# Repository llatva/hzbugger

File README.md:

# hzbugger

Hzbugger is an STM32F103C8T6-based Black Magic Probe compatible debugger by Lasse OH3HZB. 

Bottom side silkscreen created using AI tools (intended for *black PCB* as in pictures below). 

Basic functionality works out-of-box with BMP bluepill image. Extra LEDs and AUX header requires fw customization.
See [BlackMagic Probe adaptation guide](./blackmagic-probe-adaptation-guide.md) for firmware-porting and usage details.

## Schematic

<a href="./hzbugger-revA-schematic.pdf">hzbugger-revA-schematic.pdf</a>

## Getting started: Using Hzbugger to flash firmware

### Connect the probe

The device should enumerate as /dev/ttyACM0 and /dev/ttyACM1 (on Linux).

### Build the firmware

Build the application so that the output includes an ELF file containing debug information.
For example:

    build/my_application.elf

The ELF file is used both for programming the target and for debugging.
Start GDB from the shell:

    arm-none-eabi-gdb build/my_application.elf

### Flash the firmware

Then run the following commands inside GDB:

    target extended-remote /dev/ttyACM1
    monitor erase_mass
    load
    monitor reset

## Getting started: Using Hzbugger as debugger with Visual Studio Code (vscode)

### Required software

- Visual Studio Code
- ARM GNU Toolchain
- `arm-none-eabi-gdb`
- The Cortex-Debug VS Code extension

The firmware should be built with debug information enabled, for example:

    -g

For development builds, it is also useful to disable compiler optimization:

    -O0

This makes source-level debugging easier.

### Create the VS Code configuration

Create the following file in your project:

    .vscode/launch.json

Add debug configuration:

    {
        "version": "0.2.0",
        "configurations": [
            {
                "name": "Debug with Black Magic Probe",
                "type": "cortex-debug",
                "request": "launch",
                "servertype": "bmp",
                "executable": "${workspaceFolder}/build/my_application.elf",
                "device": "YOUR_MCU",
                "cwd": "${workspaceFolder}",
                "runToEntryPoint": "main"
            }
        ]
    }

Replace `YOUR_MCU` with the name of your target MCU.

Also update the `executable` path if your ELF file is located somewhere else.

### Start debugging

Connect Hzbugger and start the debugger in VS Code using `F5` button.
VS Code will use GDB to connect to the Hzbugger and start a debug session.
You can then use the normal VS Code debugging features:

- Set breakpoints
- Step over — `F10`
- Step into — `F11`
- Step out — `Shift+F11`
- Continue — `F5`
- Inspect variables
- Inspect the call stack
- Use the Watch window
- Inspect registers and memory

---

### Useful Commands

* Check the ARM GDB installation: `arm-none-eabi-gdb --version`
* Find the Hzbugger device: `ls /dev/ttyACM`
* Start GDB manually: `arm-none-eabi-gdb build/my_application.elf`
* Connect to the probe: `target extended-remote /dev/ttyACM1`
* Erase flash: `monitor erase_mass`
* Flash the firmware: `load`
* Reset the target: `monitor reset`

(Hzbugger acts as a GDB server itself so you do not need to start a separate (e.g. OpenOCD) GDB server)

## References

* Website of the Black Magic Probe: https://black-magic.org/
* BMP firmware repository: https://codeberg.org/blackmagic-debug/blackmagic

## LICENSE

CERN-OHL-S (strongly reciprocal), see [LICENSE.txt](./LICENSE.txt) for details.

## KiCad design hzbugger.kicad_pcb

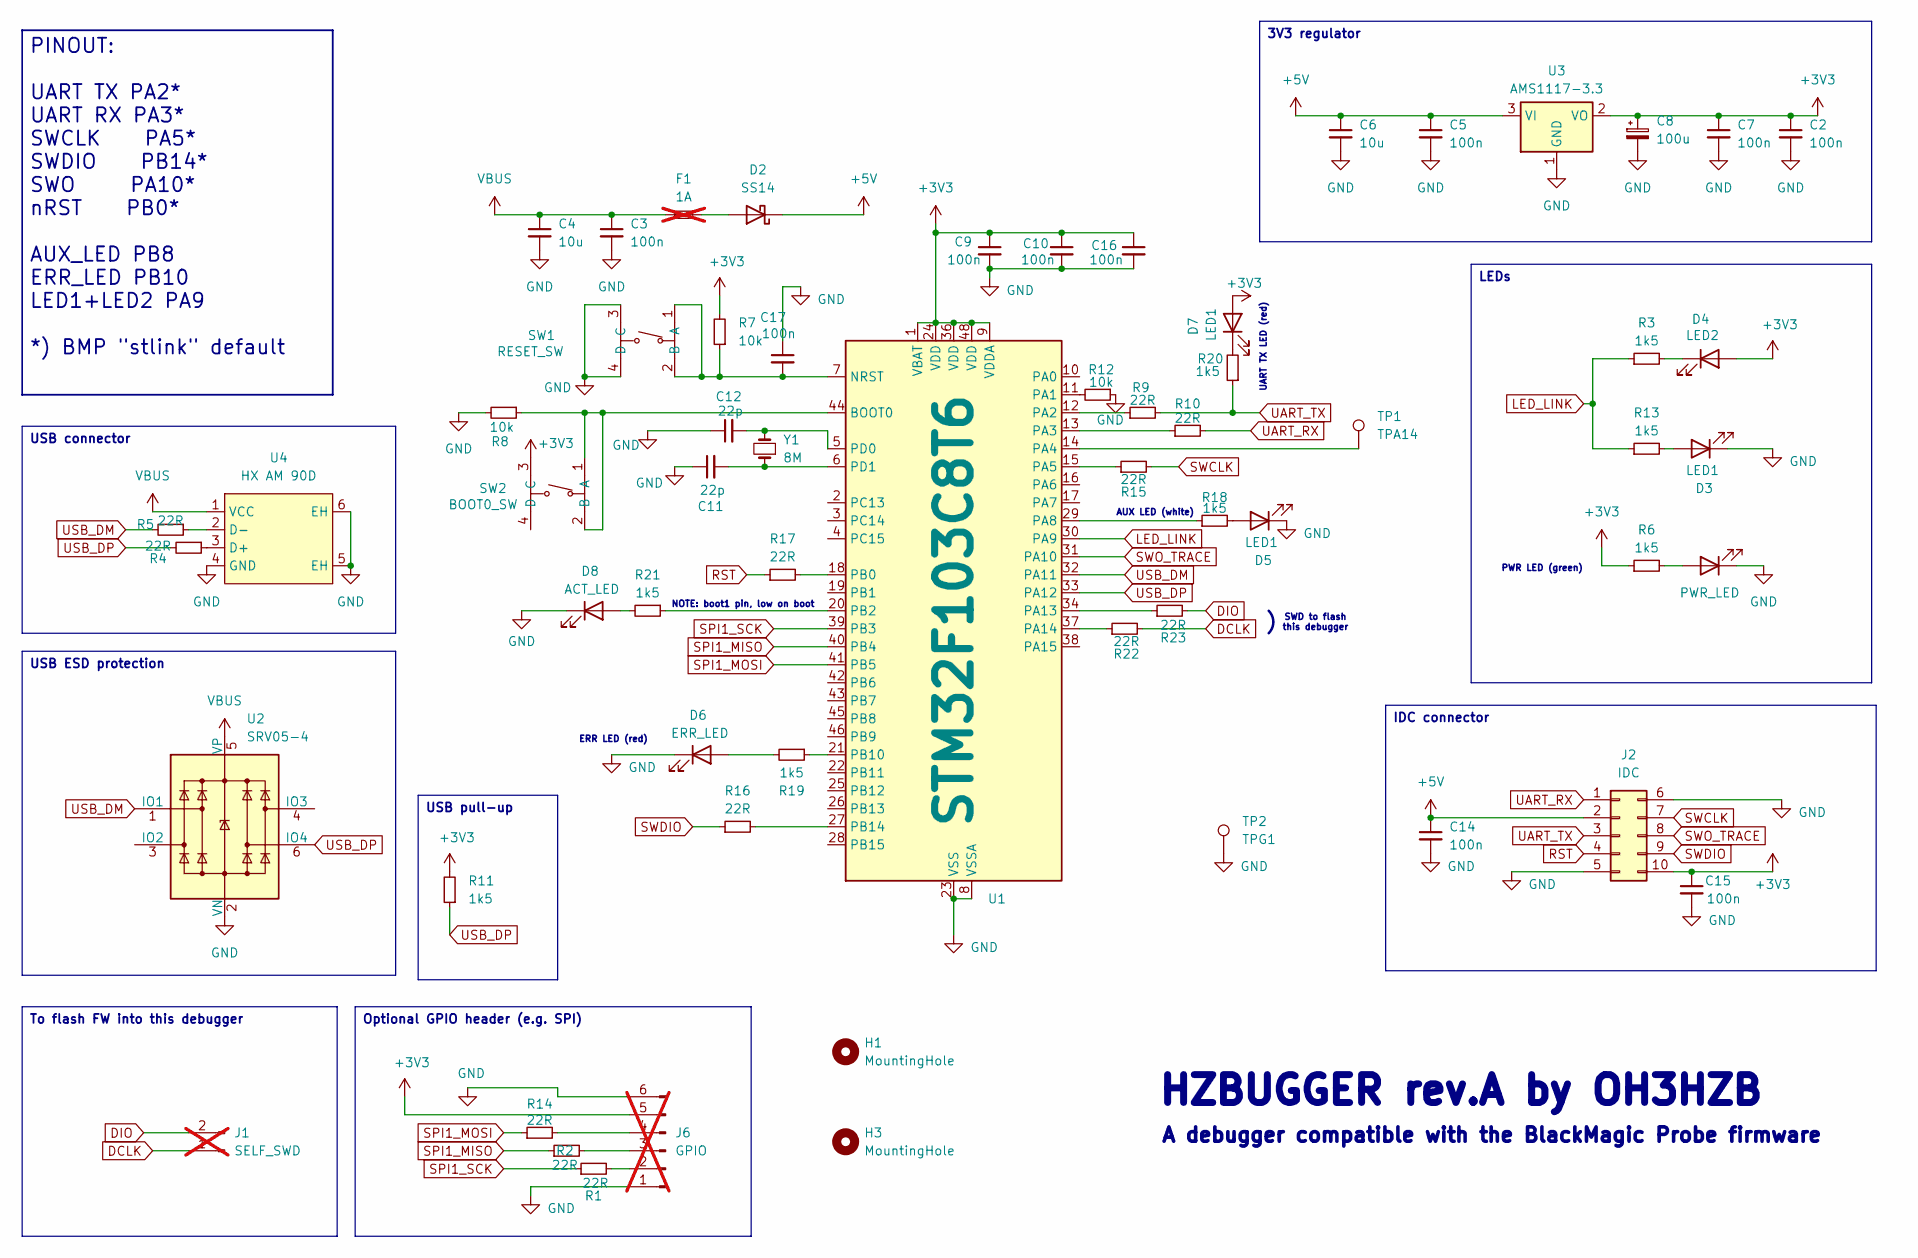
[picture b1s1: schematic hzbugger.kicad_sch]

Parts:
C2, C3, C5, C7, C9, C10, C14, C15, C16, C17: 100n; C_0603_1608Metric; LCSC C14663
C4, C6: 10u; C_0805_2012Metric; LCSC C15850
C8: 100u; CP_EIA-3528-21_Kemet-B_Pad1.50x2.35mm_HandSolder; LCSC C16133
C11, C12: 22p; C_0603_1608Metric; LCSC C1653
D1: PWR_LED; LED_0805_2012Metric; LCSC C2297
D2: SS14; D_SMA; LCSC C2480
D3, D7: LED1; LED_0603_1608Metric; LCSC C2286
D4: LED2; LED_0603_1608Metric; LCSC C2290
D5: LED1; LED_0603_1608Metric; LCSC C2290
D6: ERR_LED; LED_0603_1608Metric; LCSC C2286
D8: ACT_LED; LED_0603_1608Metric; LCSC C2290
F1: 1A; Fuse_1206_3216Metric_Pad1.42x1.75mm_HandSolder; LCSC DNP; not fitted
H1, H3: MountingHole; MountingHole_2.1mm
J1: SELF_SWD; PinHeader_1x02_P2.54mm_Vertical; LCSC DNP; not fitted
J2: IDC; SMD-pcbend-IDC-Header_2x05_P2.54mm; LCSC DNP
J6: GPIO; PinHeader_1x06_P2.54mm_Vertical; LCSC DNP; not fitted
R1, R2, R9, R10, R14, R15, R16, R17, R22, R23: 22R; R_0402_1005Metric; LCSC C25092
R3, R13, R18, R19, R20, R21: 1k5; R_0402_1005Metric; LCSC C25867
R4, R5: 22R; R_0603_1608Metric; LCSC C23345
R6: 1k5; R_0603_1608Metric_Pad0.98x0.95mm_HandSolder; LCSC C22843
R7, R8, R12: 10k; R_0402_1005Metric; LCSC C25744
R11: 1k5; R_0402_1005Metric_Pad0.72x0.64mm_HandSolder; LCSC C25867
SW1: RESET_SW; SW-SMD_4P-L5.1-W5.1-P3.70-LS6.5-TL_H1.5; LCSC C318884
SW2: BOOT0_SW; SW-SMD_4P-L5.1-W5.1-P3.70-LS6.5-TL_H1.5; LCSC C318884
TP1: TPA14; TestPoint_Pad_D1.0mm; LCSC DNP
TP2: TPG1; TestPoint_Pad_D1.0mm; LCSC DNP
U1: STM32F103C8T6; LQFP-48_7x7mm_P0.5mm; LCSC C8734
U2: SRV05-4; SOT-23-6; LCSC C7420376
U3: AMS1117-3.3; SOT-223-3_TabPin2; LCSC C6186
U4: HX AM 90D; USB-A-TH_HANXIA_HXAM90D; LCSC C5160314
Y1: 8M; Crystal_SMD_5032-2Pin_5.0x3.2mm; LCSC C115962

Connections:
+3V3: C2.1, C7.1, C8.1, C9.1, C10.1, C15.1, C16.1, D4.2 (A), D7.2 (A), J2.10, J6.5, R6.1, R7.2, R11.2, SW2.3 (C), U1.1 (VBAT), U1.9 (VDDA), U1.24 (VDD), U1.36 (VDD), U1.48 (VDD), U3.2 (VO)
+5V: C5.1, C6.1, C14.1, D2.1 (K), J2.2, U3.3 (VI)
DCLK: J1.1, R22.2
DIO: J1.2, R23.2
GND: C2.2, C3.2, C4.2, C5.2, C6.2, C7.2, C8.2, C9.2, C10.2, C11.1, C12.1, C14.2, C15.2, C16.2, C17.1, D1.1 (K), D3.1 (K), D5.1 (K), D6.1 (K), D8.1 (K), J2.5, J2.6, J6.1, J6.6, R8.2, R12.1, SW1.3 (C), SW1.4 (D), TP2.1 (1_1), U1.8 (VSSA), U1.23 (VSS), U1.35 (VSS), U1.47 (VSS), U2.2 (VN), U3.1 (GND), U4.4 (GND), U4.5 (EH), U4.6 (EH)
LED_LINK: R3.1, R13.1, U1.30 (PA9)
unnamed: D1.2 (A), R6.2
unnamed: D2.2 (A), F1.1
unnamed: D3.2 (A), R13.2
unnamed: D4.1 (K), R3.2
unnamed: D5.2 (A), R18.2
unnamed: D6.2 (A), R19.2
unnamed: D7.1 (K), R20.2
unnamed: D8.2 (A), R21.2
unnamed: J6.2, R1.2
unnamed: J6.3, R2.2
unnamed: J6.4, R14.2
unnamed: C17.2, R7.1, SW1.1 (A), SW1.2 (B), U1.7 (NRST)
unnamed: R8.1, SW2.1 (A), SW2.2 (B), U1.44 (BOOT0)
unnamed: R12.2, U1.11 (PA1)
unnamed: R9.1, U1.12 (PA2)
unnamed: R10.1, U1.13 (PA3)
unnamed: TP1.1 (1_1), U1.14 (PA4)
unnamed: R15.1, U1.15 (PA5)
unnamed: R18.1, U1.29 (PA8)
unnamed: R23.1, U1.34 (PA13)
unnamed: R22.1, U1.37 (PA14)
unnamed: R17.2, U1.18 (PB0)
unnamed: R21.1, U1.20 (PB2)
unnamed: R19.1, U1.21 (PB10)
unnamed: R16.2, U1.27 (PB14)
unnamed: C12.2, U1.5 (PD0), Y1.2
unnamed: C11.2, U1.6 (PD1), Y1.1
unnamed: R4.1, U4.3 (D+)
unnamed: R5.1, U4.2 (D-)
RST: J2.4, R17.1
SPI1_MISO: R2.1, U1.40 (PB4)
SPI1_MOSI: R14.1, U1.41 (PB5)
SPI1_SCK: R1.1, U1.39 (PB3)
SWCLK: J2.7, R15.2
SWDIO: J2.9, R16.1
SWO_TRACE: J2.8, U1.31 (PA10)
UART_RX: J2.1, R10.2
UART_TX: J2.3, R9.2, R20.1
USB_DM: R5.2, U1.32 (PA11), U2.1 (IO1)
USB_DP: R4.2, R11.1, U1.33 (PA12), U2.6 (IO4)
VBUS: C3.1, C4.1, F1.2, U2.5 (VP), U4.1 (VCC)

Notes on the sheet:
A debugger compatible with the BlackMagic Probe firmware
HZBUGGER rev.A by OH3HZB
ERR LED (red)
SWD to flash this debugger
NOTE: boot1 pin, low on boot
UART TX LED (red)
PWR LED (green)
AUX LED (white)
Optional GPIO header (e.g. SPI)
3V3 regulator
To flash FW into this debugger
USB connector
LEDs
USB pull-up
PINOUT: UART TX PA2* UART RX PA3* SWCLK PA5* SWDIO PB14* SWO PA10* nRST PB0* AUX_LED PB8 ERR_LED PB10 LED1+LED2 PA9 *) BMP "stlink" default
IDC connector
USB ESD protection

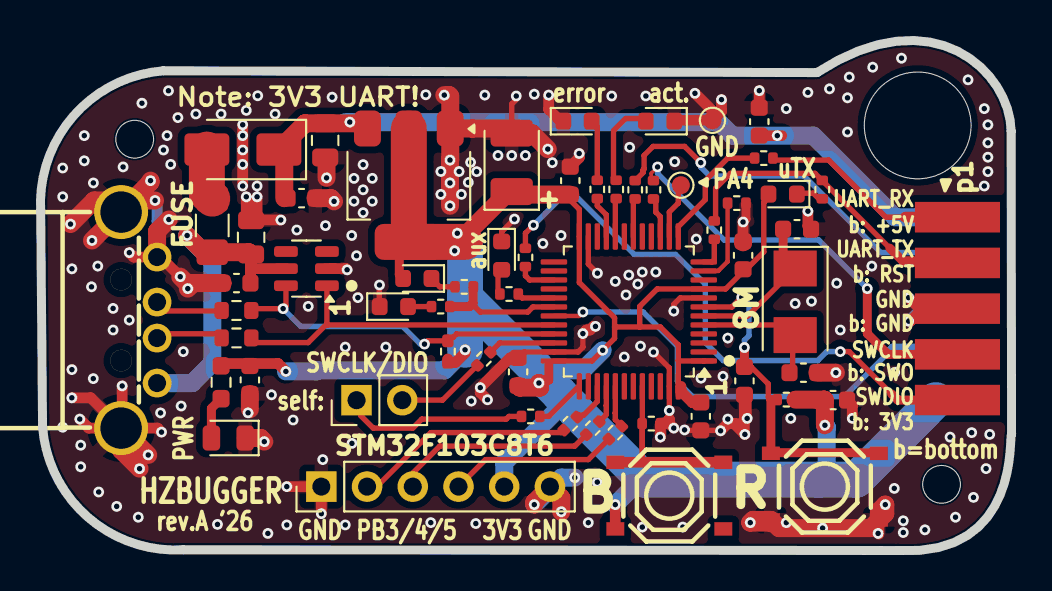
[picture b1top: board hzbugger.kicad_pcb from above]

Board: 2 copper layers, 53.9 x 28.3 mm, 61 parts (0 on the bottom side), 47 nets.

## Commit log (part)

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2026-01-01 to GH
2026-01-01 gitignore
2026-01-01 remove locks from git
2026-01-01 routing
2026-01-01 save
2026-01-01 silks
2026-01-01 to be continued
2026-01-03 silks etc
2026-01-03 silk
2026-01-04 right USB connector, etc
2026-01-04 LCSC codes
2026-01-04 show R6 3D
2026-01-04 added jlc basic tactile sw
2026-01-04 other model, reset sw now in place
2026-01-04 jlc settings for gerbers
2026-01-04 edit header footprint to remove silk lines
2026-01-06 change xtal package etc
2026-01-06 sw lcsc etc
2026-01-07 remove pinhead, just idc left
2026-01-24 layout further
2026-01-24 layout
2026-01-24 w.i.p
2026-01-24 connector
2026-01-30 gfx etc
2026-01-31 Initial plan
2026-01-31 Add Black Magic Probe adaptation guide
2026-01-31 Add STM32F103 DFU bootloader guidance
2026-01-31 Fix guide section numbering
2026-02-01 hide c8 label ä
2026-02-06 usr led
2026-02-06 minor
2026-02-06 some fine-tuning
2026-02-07 layout enhancements
2026-02-07 IDC pad lengths
2026-02-07 some final adjustments
2026-02-07 outline, to fit idc
2026-02-19 tx led
2026-02-27 final adjustments
2026-02-27 one via in wrong place
2026-03-13 hole for keychain
2026-04-30 Document verified rev.A connector pinouts and power behavior
    Agent-Logs-Url: https://github.com/llatva/hzbugger/sessions/458d2470-58cf-4c34-8422-1347c02f1809
2026-05-23 some enhancements, corrected LCSC code for 0422 1k5 R
2026-05-23 fine-tuning
